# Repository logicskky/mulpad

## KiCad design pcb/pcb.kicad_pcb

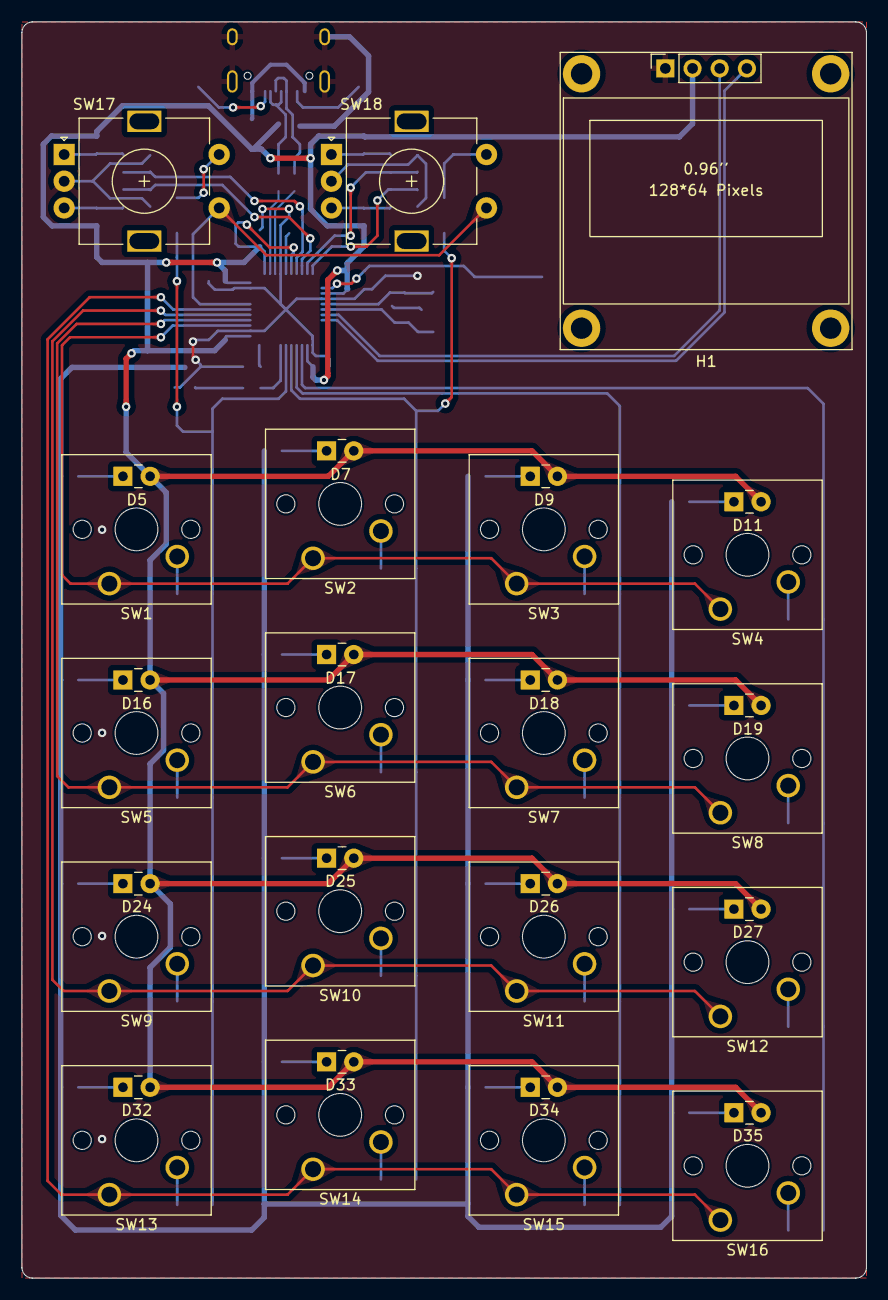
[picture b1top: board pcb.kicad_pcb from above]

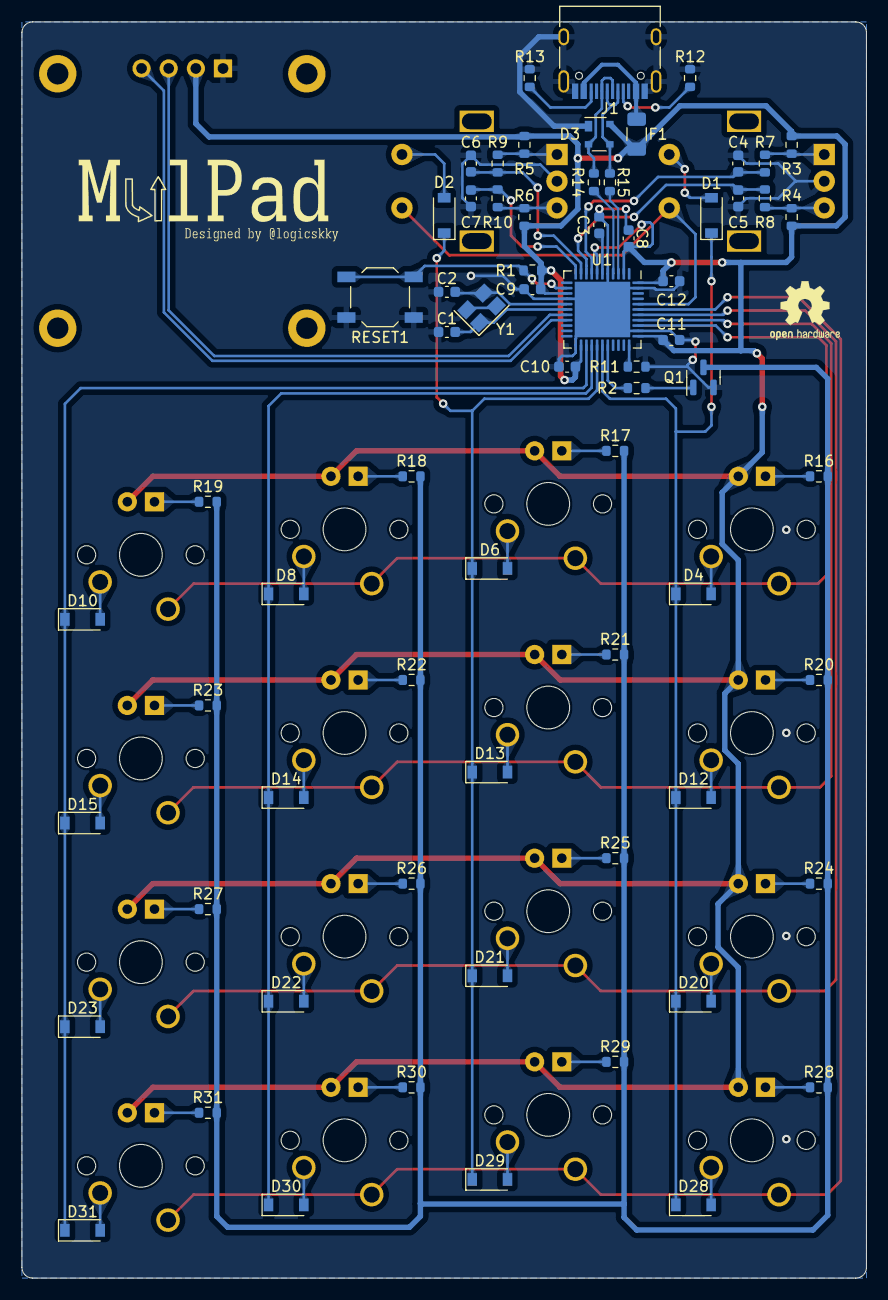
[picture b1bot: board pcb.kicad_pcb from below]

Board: 2 copper layers, 79.0 x 117.5 mm, 103 parts (68 on the bottom side), 70 nets.

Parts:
C1, C2: 22p; C_0603_1608Metric
C3: 1u; C_0603_1608Metric
C4, C5, C6, C7: 0.01u; C_0603_1608Metric
C8: 4.7u; C_0603_1608Metric
C9, C10, C11, C12: 0.1u; C_0603_1608Metric
D1, D2, D4, D6, D8, D10, D12, D13, D14, D15, D20, D21, D22, D23, D28, D29, D30, D31: 1N4148W; D_SOD-123
D3: PRTR5V0U2X; SOT-143
D5, D7, D9, D11, D16, D17, D18, D19, D24, D25, D26, D27, D32, D33, D34, D35: LED; LED_Rectangular_W3.0mm_H2.0mm
F1: MF-NSMF050-2; Fuse_1206_3216Metric
H1: OLED_I2C_SSD1306
J1: TYPE-C-31-M-12; USB_C_Receptacle_HRO_TYPE-C-31-M-12
Q1: 2N7002; SOT-23
R1, R3, R4, R5, R6, R7, R8, R9, R10, R11: 10k; R_0603_1608Metric
R2: 1k; R_0603_1608Metric
R12, R13: 5.1k; R_0603_1608Metric
R14, R15: 22; R_0603_1608Metric
R16, R17, R18, R19, R20, R21, R22, R23, R24, R25, R26, R27, R28, R29, R30, R31: 330; R_0603_1608Metric
RESET1: SW_Push; SW_SPST_TL3342
SW1, SW2, SW3, SW4, SW5, SW6, SW7, SW8, SW9, SW10, SW11, SW12, SW13, SW14, SW15, SW16: SW_Push; SW_Cherry_MX_1.00u_PCB
SW17, SW18: EC11; RotaryEncoder_Alps_EC11E-Switch_Vertical_H20mm
U1: ATmega32U4-M; QFN-44-1EP_7x7mm_P0.5mm_EP5.2x5.2mm
Y1: 16MHz_12pF; Crystal_SMD_3225-4Pin_3.2x2.5mm

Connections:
+5V: C8.1, C9.1, C10.1, C11.1, C12.1, D3.4 (VCC), D5.2 (A), D7.2 (A), D9.2 (A), D11.2 (A), D16.2 (A), D17.2 (A), D18.2 (A), D19.2 (A), D24.2 (A), D25.2 (A), D26.2 (A), D27.2 (A), D32.2 (A), D33.2 (A), D34.2 (A), D35.2 (A), F1.2, H1.2 (VCC), R1.1, R3.1, R4.1, R5.1, R6.1, U1.2 (UVCC), U1.7 (VBUS), U1.14 (VCC), U1.24 (AVCC), U1.34 (VCC), U1.44 (AVCC)
/COL0: D1.1 (K), D4.1 (K), D12.1 (K), D20.1 (K), D28.1 (K), U1.28 (PB4)
/COL1: D2.1 (K), D6.1 (K), D13.1 (K), D21.1 (K), D29.1 (K), U1.27 (PD7)
/COL2: D8.1 (K), D14.1 (K), D22.1 (K), D30.1 (K), U1.26 (PD6)
/COL3: D10.1 (K), D15.1 (K), D23.1 (K), D31.1 (K), U1.25 (PD4)
/D+: R14.2, U1.4 (D+)
/D-: R15.2, U1.3 (D-)
/EC11_1_A: C4.2, R7.1, U1.8 (PB0)
/EC11_1_B: C5.1, R8.2, U1.9 (PB1)
/EC11_2_A: C6.2, R9.1, U1.10 (PB2)
/EC11_2_B: C7.1, R10.2, U1.11 (PB3)
/LED_GND: Q1.3 (D), R16.2, R17.2, R18.2, R19.2, R20.2, R21.2, R22.2, R23.2, R24.2, R25.2, R26.2, R27.2, R28.2, R29.2, R30.2, R31.2
/ROW0: SW1.1, SW2.1, SW3.1, SW4.1, U1.36 (PF7)
/ROW1: SW5.1, SW6.1, SW7.1, SW8.1, U1.37 (PF6)
/ROW2: SW9.1, SW10.1, SW11.1, SW12.1, U1.38 (PF5)
/ROW3: SW13.1, SW14.1, SW15.1, SW16.1, U1.39 (PF4)
/ROW4: SW17.S1, SW18.S1, U1.40 (PF1)
/SCL: H1.3 (SCL), U1.18 (PD0)
/SDA: H1.4 (SDA), U1.19 (PD1)
GND: C1.2, C2.2, C3.1, C4.1, C5.2, C6.1, C7.2, C8.2, C9.2, C10.2, C11.2, C12.2, D3.1 (GND), H1.1 (GND), J1.A1 (GND), J1.A12 (GND), J1.B1 (GND), J1.B12 (GND), J1.S1 (SHIELD), Q1.2 (S), R11.2, R12.2, R13.2, RESET1.1, SW17.C, SW18.C, U1.5 (UGND), U1.15 (GND), U1.23 (GND), U1.35 (GND), U1.43 (GND), U1.45 (GND), Y1.2, Y1.4
unnamed: D1.2 (A), SW17.S2
unnamed: D2.2 (A), SW18.S2
unnamed: D3.2 (I/O1), J1.A6 (D+), J1.B6 (D+), R14.1
unnamed: D3.3 (I/O2), J1.A7 (D-), J1.B7 (D-), R15.1
unnamed: D4.2 (A), SW1.2
unnamed: D5.1 (K), R16.1
unnamed: D6.2 (A), SW2.2
unnamed: D7.1 (K), R17.1
unnamed: D8.2 (A), SW3.2
unnamed: D9.1 (K), R18.1
unnamed: D10.2 (A), SW4.2
unnamed: D11.1 (K), R19.1
unnamed: D12.2 (A), SW5.2
unnamed: D13.2 (A), SW6.2
unnamed: D14.2 (A), SW7.2
unnamed: D15.2 (A), SW8.2
unnamed: D16.1 (K), R20.1
unnamed: D17.1 (K), R21.1
unnamed: D18.1 (K), R22.1
unnamed: D19.1 (K), R23.1
unnamed: D20.2 (A), SW9.2
unnamed: D21.2 (A), SW10.2
unnamed: D22.2 (A), SW11.2
unnamed: D23.2 (A), SW12.2
unnamed: D24.1 (K), R24.1
unnamed: D25.1 (K), R25.1
unnamed: D26.1 (K), R26.1
unnamed: D27.1 (K), R27.1
unnamed: D28.2 (A), SW13.2
unnamed: D29.2 (A), SW14.2
unnamed: D30.2 (A), SW15.2
unnamed: D31.2 (A), SW16.2
unnamed: D32.1 (K), R28.1
unnamed: D33.1 (K), R29.1
unnamed: D34.1 (K), R30.1
unnamed: D35.1 (K), R31.1
unnamed: J1.A5 (CC1), R12.1
unnamed: J1.B5 (CC2), R13.1
unnamed: F1.1, J1.A4 (VBUS), J1.A9 (VBUS), J1.B4 (VBUS), J1.B9 (VBUS)
unnamed: Q1.1 (G), R2.2
unnamed: R3.2, R7.2, SW17.A
unnamed: R4.2, R8.1, SW17.B
unnamed: R5.2, R9.2, SW18.A
unnamed: R6.2, R10.1, SW18.B
unnamed: R2.1, U1.29 (PB5)
unnamed: C3.2, U1.6 (UCAP)
unnamed: C1.1, U1.17 (XTAL1), Y1.1
unnamed: C2.1, U1.16 (XTAL2), Y1.3
unnamed: R11.1, U1.33 (~HWB/PE2)
unnamed: R1.2, RESET1.2, U1.13 (~RESET)

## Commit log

2022-08-17 add .gitignore
2022-08-17 update the gitignore files
2022-08-17 add the design file of the PCB
2022-08-17 add the design files of the case and the plate
2022-08-17 add the logo
